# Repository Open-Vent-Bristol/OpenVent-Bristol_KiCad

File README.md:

OpenVent controller PCB, version A (KiCad) ported from version 2.7 (Altium,
incomplete), 2020-10-20, by Jeff Sutherland <jeffs@fomsystems.com>

All files for the Power Board are in the subfolder called "OV_Power". All control/main board files are in this folder level.
Electronic system diagram and overall device system diagram can be found here: https://docs.google.com/presentation/d/e/2PACX-1vRULcGT6Jc9GJDVb21LnrkGW9OiDjC7QJ2lRb0DsiA6KYFimniAMwYWqoMfq-0fJhvekxmhCl915fU4/pub?start=false&loop=true&delayms=3000&slide=id.gb10047446c_0_106
Also found by clicking "build" on https://openventbristol.co.uk/

Altium conversions aren't perfect but most everything is here.  Because the
schematic was incomplete and would not pass validation in Altium due to not
being complete a few things didn't make it across symbol-wise.  These will
have to be re-created in KiCad, but this is a trivial exercise.  Of more
import is the assigning of properties to all of the symbols in the schematics
so a sensible Bill of Materials may be generated directly from the schematic
or finished PCB layout.

All of the footprints that were currently in the Altium PCB came over and are
stored in the project footprint library.  These do not necessarily match the
schematic since the Altium PCB design reflects a former version of the
schematic as it had not been updated as yet.  So there is still much to do
before we can begin the process of creating the layout.  New mechanical
information is needed (see project documents).  The PCB layout for the former
version, stored for reference in the file "OpenVent_PCB-PcbDoc.kicad_pcb" does
not reflect the correct mechanical outline nor placement of components.  The
PCB footprints from the Altium design are missing information needed by KiCad
so if replacements are not available in the standard KiCad libraries then
these will have to be fixed.

TO DO's:
Complete schematic:
  a. Add BOM info to all symbols
  b. Complete circuit design
  c. Validate design

Process Board layout:
  a. load in missing footprints (use KiCad libraries, avoid creating
     footprints by hand if at all possible, if needed, fix existing ones.)
  b. Update PCB board outline, mech drill holes, and update placement and
     routing keepout areas
  c. Complete board placement and routing.
  d. Check association of footprints and 3D bodies; prepare STEP file of 3D
     image of board for mechanical group.

When creating symbols or updating fields in the schematic use the following
patterns for adding information to symbols in the lib or schemo:
   
   Field 0 is always 'Reference'
   Field 1 is always 'Value'
   Field 2 is always 'Footprint'
   Field 3 is always 'Datasheet'

These cannot be changed as they are required by the system.  The remaining
fields can be freely defined.  So in the case of OpenVent we need to
standardize how these are used to make sensible BOM generation possible.  For
example, something like this scheme could be used:

   Field 4 is defined as 'Val' (resistance, capacitance, inductance, etc.)
   Field 5 is defined as 'Voltage'
   Field 6 is defined as 'Tolerance'
   Field 7 is defined as 'Watt'  (usually just for resistors)
   Field 8 is defined as 'Current'  (usually for diodes and inductors)
   Field 9 is defined as 'Mfr' (manufacturer name)
   Field 10 is defined as 'Mfr_PN' (manufacturer's part number)
   Field 11 is defined as 'DistName' (this would be Farnell, DigiKey, etc.)
   Field 12 is defined as 'Dist_PN' (distributor's part number)
   Field 13 is defined as 'Detailed' (detailed description of part)

Optional fields can be added at will in the schematic to suit the needs of the
design or documentation efforts.

Notes on using KiCad:

  1. When setting up your KiCad installation you should also clone the
     repositories for the symbols, footprints and 3D models and refer to those
     in your 'manage libraries' settings rather than using the default
     libraries that came with your version of KiCad.  See github.com/kicad.

  2. Do not just add symbols to the design from the KiCad standard libraries.
     The symbols there are basically just "templates".  Copy standard symbols
     to a project library then add BOM and footprint info to the symbols if
     needed.

  3. Avoid creating your own footprints if at all possible.  Most every IC in
     common use already has a standard footprint in the KiCad libraries.

  4. All footprints should be kept in a local project library.  If
     modifications need to be made to paste or solder mask layers to deal with
     process issues copy footprints to another library and tag that library with
     the name of the PCB vendor so that managing artwork fudging among vendors can
     be easily sorted.

     After footprints are pulled into the PCB design from the standard KiCad
     libraries they may be exported to a local library to facilitate modifying any
     of their shapes to meet DFM requirements of a particular vendor.  Simply
     export the footprints to a project library from the PCB editor once the
     design has been transferred from the schematic and all the footprints
     have been accounted for.  There's no need to manually copy footprints
     from the KiCad libraries.

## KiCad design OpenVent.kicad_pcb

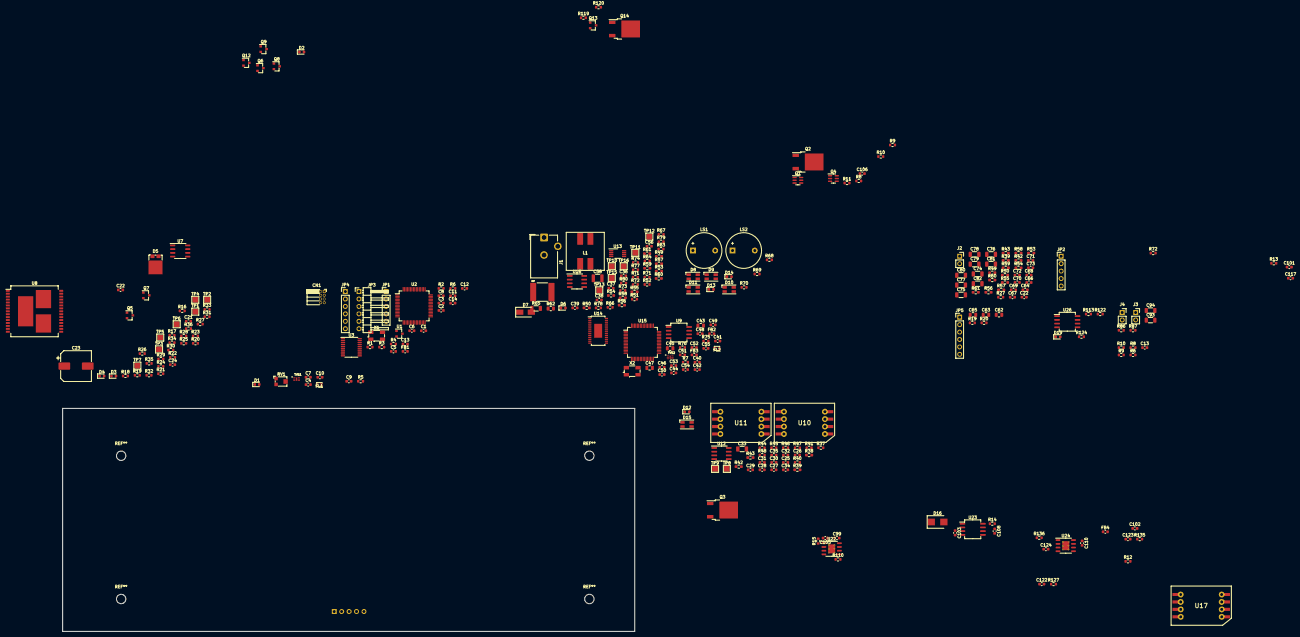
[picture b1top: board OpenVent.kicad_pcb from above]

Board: 4 copper layers, 195.5 x 76.2 mm, 290 parts (0 on the bottom side), 143 nets, no tracks yet.

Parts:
C1, C2, C3, C4, C5, C7, C8, C9, C10, C12, C14, C35, C36, C38, C40, C41, C46, C48, C49, C50, C51, C52, C53, C54, C55, C66, C122: 100nF_0603_Ceramic_Capacitor,_10%,_X7R,_25V; C_0603_1608Metric
C6, C11, C42, C44: 22pF_0603_Ceramic_Capacitor,_5%,_NP0,_50V; C_0603_1608Metric
C13, C13#2, C29, C30, C39, C68, C72, C73, C99, C103, C105, C106, C108, C110, C124: 1uF_0603_Ceramic_Capacitor,_10%,_50V,_X5R; C_0603_1608Metric
C21, C26, C28, C64, C69, C71: 470pF_0603_Ceramic_Capacitor,_5%,_100V,_C0G; C_0603_1608Metric
C22, C22#2, C24, C25, C27, C32, C37, C56, C67, C70: 10nF_0603_Ceramic_Capacitor,_10%,_50V,_X7R-; C_0603_1608Metric
C23: 1000uF_25V_Aluminium_SMD_Capacitor,_20%; CP_Elec_10x10
C31: 33nF_0603_Ceramic_Capacitor,_10%,_50V; C_0603_1608Metric
C33: 22uF_1206_Ceramic_Capacitor,_10%,_10V,_X7R; C_1206_3216Metric
C34: 033uF_0603_Ceramic_Capacitor,_10%,_16V; C_0603_1608Metric
C43, C45, C47, C62, C63, C65: 10uF_0805_Ceramic_Capacitor_10%_X7R_10V; C_0805_2012Metric
C57: 2.2uF_2824_film_capacitor_10%_40V; CAPPC7360X380N
C58: C_1210_10uF_25V_10%_X7R; C_1210_3225Metric
C74, C75, C76, C77, C78, C79, C80, C81, C82: C_1206_47nF_16V_2%_PPS_film; C_1206_3216Metric
C93, C94: 22uF_1206_Ceramic_Capacitor,_10%,_10V,_X7R; R_1206_3216Metric
C101, C102, C117, C123: 2.2uF_0603_Ceramic_Capacitor,_10%,_50V,_X5R; C_0603_1608Metric
CN1: 2x5_Way_1.27mm_Pitch_Header_MCU; PinSocket_2x04_P1.27mm_Horizontal
D1, D2, D3, D6, D12, D14, D19: LED_GREEN_0603_SMD; LED_0603_1608Metric
D4, D13: LED_Red_0603_SMD; LED_0603_1608Metric
D5: FSV20100V; TO-277A
D7: DIODE_GEN_PURP_1KV_1A_SMA; D_SMA
D8, D9, D10, D11, D15: BB-HRGB32M-TRB; LED_RGB_BL-RRGB32M_TRB_PLCC4_3.2x2.8mm
D16: MBRS260T3G; D_SMB
FB1, FB2, FB3: Chip_Ferrite,_600R,_0603,_750mA; L_0603_1608Metric
FB4: BLM18AG601SN1D Chip_Ferrite,_600R,_0603,_750mA; C_0603_1608Metric
FL1, FL2: DLP11SA900HL2L; Murata_DLP11S
J1: OpenVent_Barrel_Connector; BarrelJack_CUI_PJ-102AH_Horizontal
J2, J3, J4: Conn_01x02; PinSocket_1x02_P2.54mm_Vertical
JP1, JP2, JP2#2: Pin_Header,_1x5-Way,_2.54mm_Pitch; PinHeader_1x05_P2.54mm_Vertical
JP3: Pin_Header,_1x6-Way,_2.54mm_Pitch, Mpn 640456-6; PinHeader_1x06_P2.54mm_Horizontal
JP4, JP5: Pin_Header,_1x6-Way,_2.54mm_Pitch; PinHeader_1x06_P2.54mm_Vertical
L1: MSD1260-333; MSD1260
LS1, LS2: AUDIO_MAGNETIC_INDICATOR; Buzzer_12x9.5RM7.6
Q1, Q4: DMMT5401-7-F; SC-74-6_1.5x2.9mm_P0.95mm
Q2, Q3, Q14: AOD4185; TO-252-2
Q5, Q6, Q7, Q9, Q12, Q13: 2N7002BK; SOT-23
Q8: SSM3K341R; SOT-23
R1, R2, R3: R_0603_2k74_0.1W_0.1%; R_0603_1608Metric
R4, R9, R9#2, R11, R12, R21, R22, R26, R28, R31, R71, R73, R74, R75, R76: 1K_0603_Chip_Resistor,_1%,_0.1W; R_0603_1608Metric
R5, R6, R6#2, R16, R18, R52, R119, R120, R124: 10k_0603_Chip_Resistor,_1%,_0.1W; R_0603_1608Metric
R7, R72, R72#2, R86, R87: 12k_0603_Chip_Resistor,_1%,_0.1W; R_0603_1608Metric
R8, R8#2, R10, R10#2, R29, R68, R69, R110, R127: 100K_0603_Chip_Resistor,_1%,_0.1W; R_0603_1608Metric
R13, R14, R15, R36, R113, R122, R135, R136: 0R1_0603_Chip_Resistor,_1%,_0.1W; R_0603_1608Metric
R17, R23, R37, R41, R67: 215k_0603_Chip_Resistor,_1%,_0.1W; R_0603_1608Metric
R19, R19#2, R20, R20#2: 2k4_0603_Chip_Resistor,_1%,_0.1W; R_0603_1608Metric
R24, R25: 4k7_0603_Chip_Resistor,_1%,_0.1W; R_0603_1608Metric
R27, R27#2: 18k_0603_Chip_Resistor,_1%,_0.1W; R_0603_1608Metric
R30, R32, R35: 30k_0603_Chip_Resistor,_1%,_0.1W; R_0603_1608Metric
R33, R34: 20k_0603_Chip_Resistor,_1%,_0.1W; R_0603_1608Metric
R38, R39, R39#2, R42, R42#2, R43, R43#2, R49, R49#2, R50, R50#2, R53, R53#2, R54, R54#2, R55, R55#2, R56, R56#2, R57, R57#2, R58, R58#2, R59, R59#2, R60, R60#2, R61, R61#2: R_0603_47K_0.1%_0.1W_Film; R_0603_1608Metric_Pad0.98x0.95mm_HandSolder
R40, R44, R66: 1M_0603_Chip_Resistor,_1%,_0.1W; R_0603_1608Metric
R45, R46: 3k6_0603_Chip_Resistor,_1%,_0.1W; R_0603_1608Metric
R47, R48: 180k_0603_Chip_Resistor,_1%,_0.1W; R_0603_1608Metric
R51: 634R_0603_Chip_Resistor,_1%,_0.1W; R_0603_1608Metric
R62: R_0805_050m_cursense; R_0805_2012Metric
R63: R_0603_015m_cursense; R_0603_1608Metric
R64: R_0603_49k9_0.1W_1%; R_0603_1608Metric
R65: R_1206_250m_cursense; R_1206_3216Metric
R70: 10R_0603_Chip_Resistor,_1%,_0.1W; R_0603_1608Metric
R77: R_0603_113k_0.1W_1%; R_0603_1608Metric
R78: R_0603_30k1_0.1W_1%; R_0603_1608Metric
R79: R_0603_95k3_0.1W_1%; R_0603_1608Metric
R80: R_0603_10k2_0.1W_1%; R_0603_1608Metric
RT1: R_Thermistor_0603_10K_NTC; R_0603_1608Metric
RV1: RES_trimpot_10K_SMD; Potentiometer_Bourns_TC33X_Vertical
TP1, TP2, TP3, TP4, TP5, TP6, TP7, TP8, TP9, TP10, TP11, TP12, TP13, TP15, TP16: Test_Point_PTH; TestPoint_Pad_2.0x2.0mm
TVS1, TVS2: RClamp3654P.TCT; SON50P160X160X65-7N
U1: TMP236A4DBZT; SOT-23
U2: STM32L476RGLQFP64; LQFP-64_10x10mm_P0.5mm
U3: TI_TXB0108PWR; TSSOP-20_4.4x6.5mm_P0.65mm
U7: LMC6772AIMX; SO-8_3.9x4.9mm_P1.27mm
U8: VNH5019ATR-E; ST_MultiPowerSO-30
U9, U23, U26: LDL212D33R; SO-8_5.3x6.2mm_P1.27mm
U10, U17: MPXV4006GP; NXP-CASE-1369_482C
U11: MPXV4006DP; NXP-CASE-1351-482C
U12, U16: TLV2333IDR; SOIC-8_3.9x4.9mm_P1.27mm
U13: TLV7042DGKR; VSSOP-8_3.0x3.0mm_P0.65mm
U14: LT3796; TSSOP-28-LTvar_EB_4.4x9.7mm_P0.65mm
U15: FT2232HL-REEL; LQFP-64_10x10mm_P0.5mm
U22, U24: BD50FC0WEFJ-E2; HSOP-8-1EP_3.9x4.9mm_P1.27mm_EP2.41x3.1mm_ThermalVias
X1: ABM3B-16.000MHZ; Crystal_SMD_Abracon_ABM3B-4Pin_5.0x3.2mm
X2: ABM3B-12.000MHZ; Crystal_SMD_Abracon_ABM3B-4Pin_5.0x3.2mm

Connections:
+3.3V: C65.1, C123.1, R122.2, R135.2
+3V3: C2.2, C41.1, C106.2, C117.1, C122.2, CN1.1, FB2.1, FB3.1, JP1.2, JP3.6, R13.2, R19.2, R19#2.2, R20.2, R20#2.2, R24.2, R25.2, R52.1, R71.1, R73.1, R76.1, R86.1, R87.1, R119.2, TP10.1, U1.1, U3.2, U3.10, U7.6, U13.8, U15.20, U15.31, U15.42, U15.50, U15.56
+5V: C12.2, C14.2, C22.2, C22#2.2, C25.2, C27.2, C29.2, C30.2, C35.2, C62.1, C63.1, C67.2, C68.2, C70.2, C72.2, C73.2, C99.2, C101.1, C102.1, C105.2, C110.2, C124.2, D8.1, D9.1, D10.1, D11.1, D15.1, FB4.1, JP1.1, LS1.1, LS2.1, R1.1, R3.1, R15.2, R29.2, R69.2, R113.2, R120.2, R136.2, RV1.1, TP11.1, U3.19, U7.8, U10.2, U12.8, U17.2, U22.8, U24.8, U26.4
/JTAG/J_3V3: C52.1, C53.1, C54.1, C55.1, U9.1, U9.8
/Microcontroller/ANALOG-SPARE: JP1.3, U2.17
/Microcontroller/BUZZER_PWM: R8.1, R8#2.1, U2.16
/Microcontroller/USB-DM: FL1.2, TVS1.1, U2.44
/Microcontroller/USB-DP: FL1.3, TVS1.2, U2.45
/Microcontroller/XTAL-1: C6.2, U2.5, X1.1
/Microcontroller/XTAL-2: C11.2, U2.6, X1.3
/Power_Supplies/3v3_S: R122.1, U26.1, U26.8
AD_VREF: C75.1, R38.2
FLOW_SENS_DRCT: C69.2, R37.1, R57.1, R57#2.1
FLOW_SENS_GAIN: C32.1, R44.2, R58.1, R58#2.1, U12.7
GND: C1.1, C2.1, C3.1, C4.1, C5.1, C6.1, C7.1, C8.1, C9.1, C10.1, C11.1, C12.1, C13.1, C13#2.1, C14.1, C22.1, C22#2.1, C25.1, C26.1, C27.1, C28.1, C29.1, C30.1, C31.2, C33.2, C35.1, C36.2, C37.2, C38.2, C39.2, C40.2, C41.2, C42.2, C43.2, C44.2, C45.2, C46.2, C47.2, C48.2, C49.2, C50.2, C51.2, C52.2, C53.2, C54.2, C55.2, C56.2, C58.2, C62.2, C63.2, C64.1, C65.2, C66.1, C67.1, C68.1, C69.1, C70.1, C71.1, C72.1, C73.1, C74.2, C75.2, C76.2, C77.2, C78.2, C79.2, C80.2, C81.2, C82.2, C93.2, C94.2, C99.1, C101.2, C102.2, C103.1, C105.1, C106.1, C108.2, C110.1, C117.2, C122.1, C123.2, C124.1, CN1.3, CN1.5, D1.2, D5.1, D5.2, D8.3, D9.3, D10.3, D11.3, D12.2, D14.2, D15.3, J1.2, J2.2, JP1.4, JP1.5, JP2.1, JP2#2.1, JP3.5, JP4.1, JP5.1, L1.4, Q5.2, Q9.2, Q12.2, R2.2, R7.1, R8.2, R8#2.2, R10.2, R10#2.2, R11.1, R12.1, R18.2, R27.1, R27#2.1, R33.2, R34.2, R40.1, R41.1, R46.1, R47.2, R63.1, R67.2, R68.2, R70.2, R72.1, R72#2.1, R74.1, R75.1, R80.2, R110.1, RV1.3, TP2.1, TP9.1, TP13.1, TP16.1, TVS1.7, TVS2.7, U1.3, U2.12, U2.18, U2.31, U2.47, U2.63, U3.11, U7.4, U7.5, U9.2, U9.3, U9.6, U9.7, U10.3, U11.3, U12.4, U13.4, U14.4, U14.13, U14.17, U14.21, U14.22, U14.29, U15.1, U15.5, U15.10, U15.11, U15.13, U15.15, U15.25, U15.35, U15.47, U15.51, U16.4, U17.3, U22.3, U22.9, U23.2, U23.3, U23.6, U23.7, U24.3, U24.9, U26.2, U26.3, U26.6, U26.7
I2C_SCL: R20.1, R20#2.1
I2C_SDA: R19.1, R19#2.1
LDO-EN: R110.2, U22.5, U24.5
MOTOR-CURRENT: C21.2, R23.1, TP3.1, U2.9, U7.1
MOTOR-IN-B: R21.1, U2.34
NRST_M: R6.1, R6#2.1, U2.7
unnamed: C3.2, FB1.2, U2.13
unnamed: C13.2, C13#2.2, R9.1, R9#2.1
unnamed: C21.1, R18.1, R23.2, U7.2
unnamed: C24.1, Q7.1, R34.1, R35.1, TP7.1
unnamed: C31.1, R37.2, R40.2, U12.5
unnamed: C32.2, R41.2, R44.1, U12.6
unnamed: C33.1, R45.2, R47.1, U12.3
unnamed: C34.1, R46.2, R48.1, U12.2
unnamed: C36.1, R52.2, U13.3
unnamed: C37.1, U14.28
unnamed: C38.1, U14.11
unnamed: C40.1, U9.4, U9.5
unnamed: C42.1, U15.2, X2.1
unnamed: C43.1, C46.1, FB3.2, U15.4
unnamed: C44.1, U15.3, X2.3
unnamed: C47.1, C48.1, FB2.2, U15.9
unnamed: C57.1, L1.1, Q8.3
unnamed: C57.2, D16.2, L1.2
unnamed: C58.1, D16.1, R65.1, U14.1
unnamed: C74.1, FB4.2
unnamed: C103.2, U23.4, U23.5
unnamed: U8.15, U8.16, U8.21
unnamed: U8.1, U8.25, U8.30
unnamed: D1.1, R4.1
unnamed: Q1.5, Q2.3, Q3.3, Q4.5
unnamed: D5.3, R36.1
unnamed: D7.1, R65.2, R78.1, RT1.1, U14.2
unnamed: D10.2, D11.4
unnamed: D9.2, D10.4
unnamed: D11.2, U15.60
unnamed: FL2.2, TVS2.1, U15.7
unnamed: FL2.3, TVS2.2, U15.8
unnamed: J2.1, R45.1, TP8.1
unnamed: JP2.2, JP2#2.2
unnamed: JP2.3, JP2#2.3
unnamed: JP2.4, JP2#2.4
unnamed: JP2.5, JP2#2.5
unnamed: L1.3, R62.2, U14.26
unnamed: LS1.2, LS2.2, Q13.3
unnamed: Q1.1, Q1.2, Q1.3
unnamed: Q1.4, Q3.1
unnamed: Q2.1, Q4.4
unnamed: Q4.1, Q4.2, Q4.3
unnamed: Q5.3, Q6.1, R29.1
unnamed: Q6.2, Q7.2, R33.1, TP6.1
unnamed: Q7.3, R32.1, TP5.1
unnamed: Q8.1, U14.19
unnamed: Q8.2, R63.2, U14.18
unnamed: Q9.1, R68.1
unnamed: Q12.1, R64.2, U14.16
unnamed: Q12.3, R77.2
unnamed: Q9.3, Q13.1, R69.1
unnamed: Q6.3, Q14.1, R30.1, TP4.1
unnamed: R1.2, R2.1, R3.2
unnamed: R4.2, U2.4
unnamed: R5.1, U2.60
unnamed: R7.2, U15.6
unnamed: R9.2, R9#2.2, R10.1, R10#2.1
unnamed: R14.1, U23.1, U23.8
unnamed: R15.1, U22.1
unnamed: R16.1, R17.1, U7.3
unnamed: R16.2, TP1.1, U8.18, U8.19, U8.20, U8.26, U8.27, U8.28
unnamed: R21.2, U8.10
unnamed: R22.2, U8.7
unnamed: R27.2, R27#2.2
unnamed: R39.2, R39#2.2
unnamed: R42.2, R42#2.2
unnamed: R43.2, R43#2.2
unnamed: R49.2, R49#2.2, U13.2
unnamed: R50.2, R50#2.2
unnamed: R53.2, R53#2.2, U14.6
unnamed: R54.2, R54#2.2
unnamed: R64.1, U14.20
unnamed: R66.2, R67.1, U16.3
unnamed: R71.2, U13.6
unnamed: R72.2, R72#2.2, U13.5
unnamed: R73.2, U16.6
unnamed: R74.2, U16.5
unnamed: R75.2, U15.61
unnamed: R76.2, U15.14
unnamed: R77.1, R79.2, R80.1, U14.7
unnamed: R78.2, R79.1, RT1.2
unnamed: R136.1, U24.1
unnamed: U2.28, U3.4
unnamed: U2.56, U3.6
unnamed: U2.57, U3.7
unnamed: U2.58, U3.8
unnamed: U2.59, U3.9
unnamed: U14.9, U14.10, U14.14
O2_SENS: C34.2, R48.2, R59.1, R59#2.1, U12.1
PB_SEL_MCU: R28.2, U2.14
PRES_SENS_PAT: C71.2, R56.1, R56#2.1, U10.4
PRES_SENS_VENT: C64.2, R55.1, R55#2.1, U17.4
PWM: R22.1, U2.15
SOUNDER-CURRENT: Q13.2, R70.1
SPI1_FPGA_CS: JP3.4, U2.20
SPI1_MISO: JP3.3, U2.22
SPI1_MOSI: JP3.2, U2.23
SPI1_SCLK: JP3.1, U2.21
SensorOut_F: R60.1, R60#2.1
SensorOut_G: R61.1, R61#2.1
TCK_M: CN1.4, U2.49
TDI_M: CN1.8, U2.50
TDO_M: CN1.6, U2.55
TMS_M: CN1.2, U2.46
V1V8: C45.1, C49.1, C50.1, C51.1, U15.12, U15.37, U15.49, U15.64
VBATT-SCALED: U2.10, U16.1, U16.2
VBUS: C39.1, D7.2, Q4.6, R66.1, TP12.1, TP15.1
VDC: C4.2, C5.2, C7.2, C8.2, C9.2, C10.2, C108.1, D2.1, D19.1, R5.2, R6.2, R6#2.2, R14.2, R124.2, U2.1, U2.19, U2.32, U2.48, U2.64, U16.8
VIN: J1.1, R51.1, R62.1, U14.23, U14.25
VIN_FAIL_M: R124.1, U2.61
VMEM: C1.2, Q1.6, TVS1.6
VMOTOR: C24.2, R35.2, R36.2, U8.3, U8.12, U8.13, U8.23
Vcap_F: C81.1, R53.1, R53#2.1, R60.2, R60#2.2
Vcap_FLOW_SENS_DRCT: C78.1, R43.1, R43#2.1, R57.2, R57#2.2
Vcap_FLOW_SENS_GAIN: C79.1, R49.1, R49#2.1, R58.2, R58#2.2
Vcap_G: C82.1, R54.1, R54#2.1, R61.2, R61#2.2
Vcap_O2_SENS: C80.1, R50.1, R50#2.1, R59.2, R59#2.2
Vcap_PRES_SENS_PAT: C77.1, R42.1, R42#2.1, R56.2, R56#2.2
Vcap_PRES_SENS_VENT: C76.1, R39.1, R39#2.1, R55.2, R55#2.2
nMOTOR-FAULT-A: R25.1, U2.37, U8.5
nMOTOR-FAULT-B: R24.1, U2.25, U8.9

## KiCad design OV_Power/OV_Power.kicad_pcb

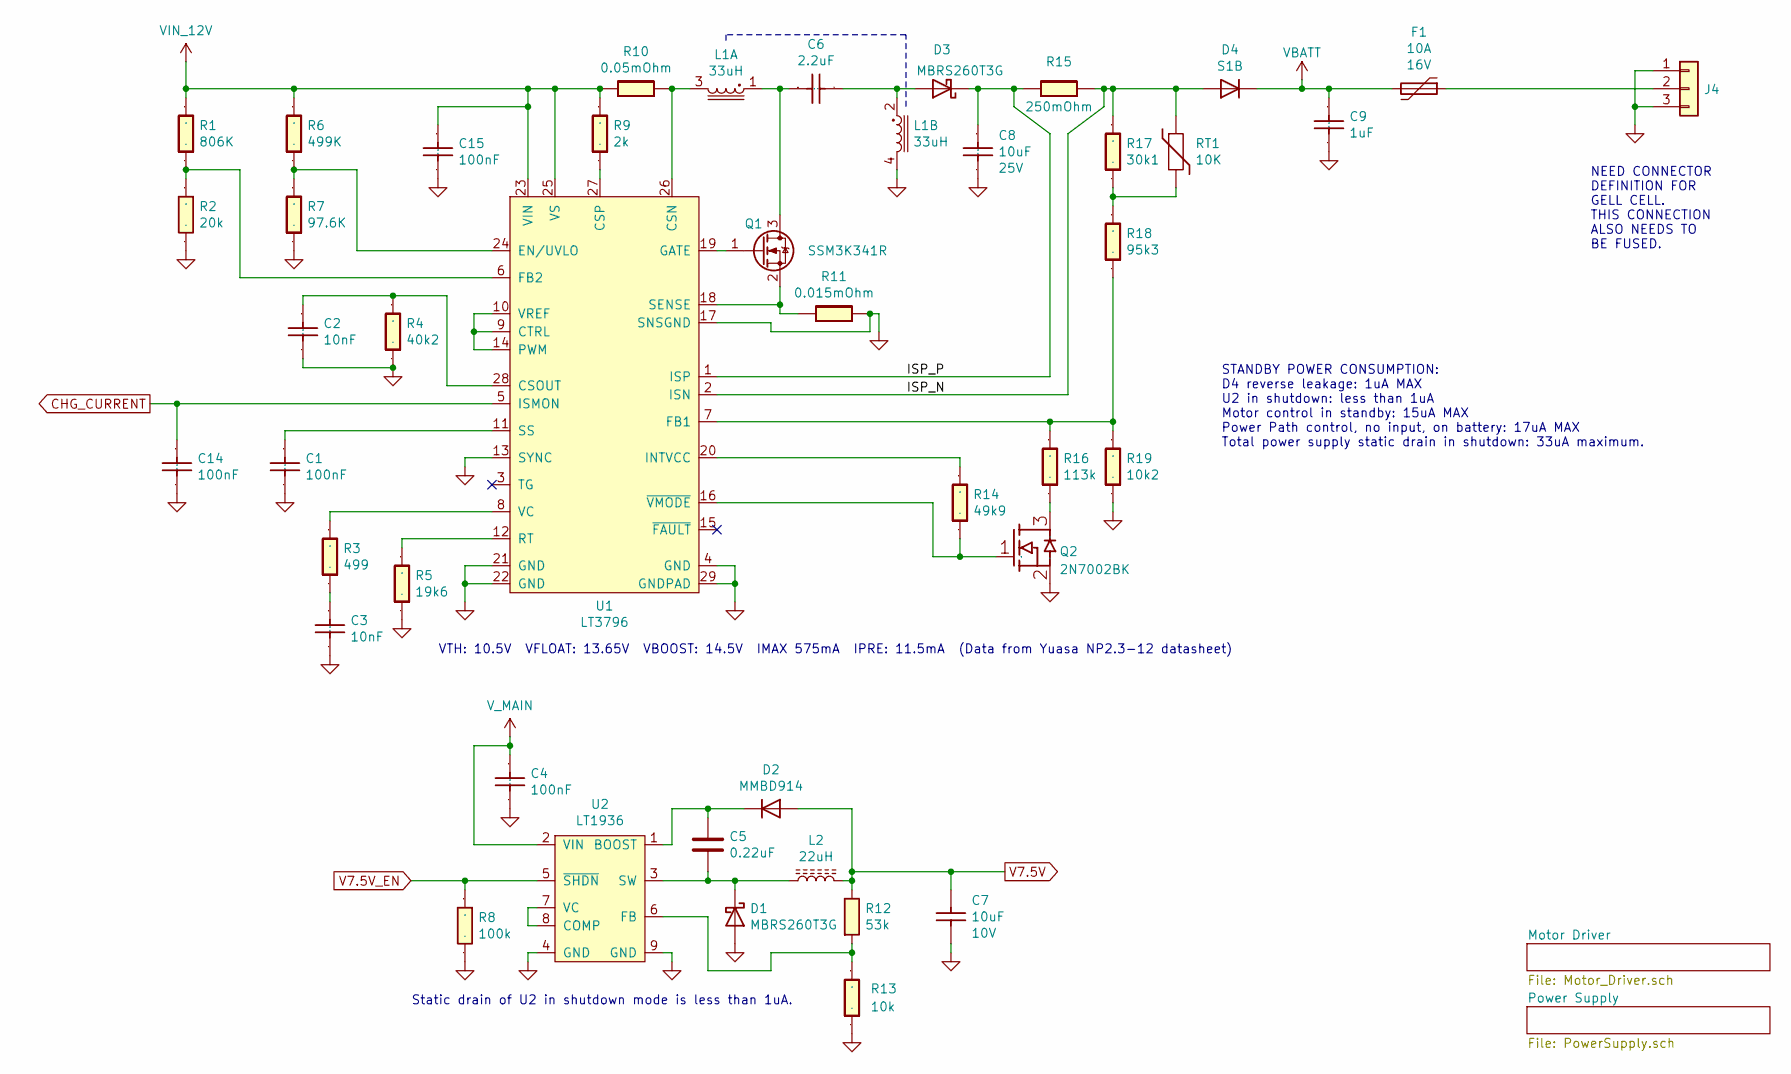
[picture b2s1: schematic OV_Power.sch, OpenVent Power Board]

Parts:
C1, C4, C14, C15: 100nF_0603_Ceramic_Capacitor,_10%,_X7R,_25V; C_0603_1608Metric; Voltage 25V; Tolerance 10%
C2, C3: 10nF_0603_Ceramic_Capacitor,_10%,_50V,_X7R-; C_0603_1608Metric; Voltage 50V; Tolerance 10%
C5: C_0603_0.22uf_25V_10%; C_0603_1608Metric; Tolerance 10%; Voltage 25V; Mfr_PN GCM188R71E224KA55J
C6: 2.2uF_2824_film_capacitor_10%_40V; CAPPC7360X380N; Voltage 63V; Tolerance 10%; Mfr_PN SMDTC04220TB00KQ00
C7: 10uF_0805_Ceramic_Capacitor_10%_X7R_10V; C_0805_2012Metric; Voltage 10V; Tolerance 10%; Mfr_PN GCM21BR71A106KE22L
C8: C_1210_10uF_25V_10%_X7R; C_1210_3225Metric; Voltage 25V; Tolerance 10%; Mfr_PN CL32A106KAULNNE
C9: 1uF_0603_Ceramic_Capacitor,_10%,_50V,_X5R; C_0603_1608Metric; Voltage 50V; Tolerance 10%
D1, D3: MBRS260T3G; D_SMB; Voltage 60V; Mfr_PN MBRS260T3G
D2: MMBD914; SOT-23; Voltage 100V; Mfr_PN MMBD914-E3-08
D4: S1B; D_SMA; Voltage 100V; Mfr_PN S1B
F1: Polyfuse_10A; LF_16R1000G; Voltage 16V; Mfr_PN 16R1000GMR
J4: Conn_01x03_JST_B3P_Vert; JST_B3P-VH(LF)(SN); Mfr_PN B3P-VH(LF)(SN)
L1: MSD1260-333; MSD1260; Mfr_PN MSD1260-333MLB
L2: L_22uH_2.6A_42mOhm_SMT; L-Bourns-SRU1048-series; Mfr_PN SRU1048-220Y
Q1: SSM3K341R; SOT-23; Mfr_PN SSM3K341R,LF
Q2: 2N7002BK; SOT-23; Voltage 60V; Mfr_PN 2N7002BK,215
R1: R_0603_806K_0.1W_1%; R_0603_1608Metric; Tolerance 1%
R2: 20k_0603_Chip_Resistor,_1%,_0.1W; R_0603_1608Metric; Tolerance 1%
R3: R_0603_499R_0.1W_1%; R_0603_1608Metric; Tolerance 1%
R4: R_0603_40k2K_0.1W_1%; R_0603_1608Metric; Tolerance 1%
R5: R_0603_19k6_0.1W_1%; R_0603_1608Metric; Tolerance 1%
R6: R_0603_499K_0.1W_1%; R_0603_1608Metric; Tolerance 1%
R7: R_0603_97.6K_0.1W_1%; R_0603_1608Metric; Tolerance 1%
R8: 100K_0603_Chip_Resistor,_1%,_0.1W; R_0603_1608Metric; Tolerance 1%
R9: R_0603_2k_0.1W_1%; R_0603_1608Metric; Tolerance 1%
R10: R_0805_050m_cursense; R_0805_2012Metric; Tolerance 1%; Mfr_PN KDV08FR050ET
R11: R_0603_015m_cursense; R_0603_1608Metric; Tolerance 1%; Mfr_PN LVT06R0150FER
R12: R_0603_53K_0.1W_1%; R_0603_1608Metric; Tolerance 1%; Mfr_PN RN73H1JTTD5302F25
R13: 10k_0603_Chip_Resistor,_1%,_0.1W; C_0603_1608Metric; Tolerance 1%
R14: R_0603_49k9_0.1W_1%; R_0603_1608Metric; Tolerance 1%
R15: R_1206_250m_cursense; R_1206_3216Metric; Tolerance 1%; Mfr_PN PT1206FR-7W0R25L
R16: R_0603_113k_0.1W_1%; R_0603_1608Metric; Tolerance 1%
R17: R_0603_30k1_0.1W_1%; R_0603_1608Metric; Tolerance 1%
R18: R_0603_95k3_0.1W_1%; R_0603_1608Metric; Tolerance 1%
R19: R_0603_10k2_0.1W_1%; R_0603_1608Metric; Tolerance 1%
RT1: R_Thermistor_0603_10K_NTC; R_0603_1608Metric; Tolerance 5%; Mfr_PN NTHS0603N02N1002JE
U1: LT3796; TSSOP-28-LTvar_EB_4.4x9.7mm_P0.65mm; Mfr_PN LT3796IFE-1#TRPBF
U2: LT1936; LT_MS8E; Mfr_PN LT1936EMS8E#PBF

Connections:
/ISP_N: D4.2 (A), R15.2, R17.1, RT1.1, U1.2 (ISN)
/ISP_P: C8.1, D3.1 (K), R15.1, U1.1 (ISP)
CHG_CURRENT: C14.1, U1.5 (ISMON); also elsewhere on the board
GND: C1.2, C2.2, C3.2, C4.2, C7.2, C8.2, C9.2, C14.2, C15.2, D1.2 (A), J4.1, J4.3, L1.4, Q2.2 (S), R2.2, R4.2, R5.2, R7.2, R8.2, R11.1, R13.2, R19.2, U1.4 (GND), U1.13 (SYNC), U1.17 (SNSGND), U1.21 (GND), U1.22 (GND), U1.29 (GNDPAD), U2.4 (GND), U2.9 (GND); also elsewhere on the board
unnamed: C1.1, U1.11 (SS)
unnamed: C2.1, R4.1, U1.28 (CSOUT)
unnamed: C3.1, R3.2
unnamed: C5.1, D2.3 (K), U2.1 (BOOST)
unnamed: C5.2, D1.1 (K), L2.1, U2.3 (SW)
unnamed: C6.1, L1.1 (2), Q1.3 (D)
unnamed: C6.2, D3.2 (A), L1.2
unnamed: F1.1, J4.2
unnamed: L1.3 (4), R10.2, U1.26 (CSN)
unnamed: Q1.1 (G), U1.19 (GATE)
unnamed: Q1.2 (S), R11.2, U1.18 (SENSE)
unnamed: Q2.1 (G1), R14.2, U1.16 (~VMODE~)
unnamed: Q2.3 (D), R16.2
unnamed: R1.2, R2.1, U1.6 (FB2)
unnamed: R3.1, U1.8 (VC)
unnamed: R5.1, U1.12 (RT)
unnamed: R6.2, R7.1, U1.24 (EN/UVLO)
unnamed: R9.2, U1.27 (CSP)
unnamed: R12.2, R13.1, U2.6 (FB)
unnamed: R14.1, U1.20 (INTVCC)
unnamed: R16.1, R18.2, R19.1, U1.7 (FB1)
unnamed: R17.2, R18.1, RT1.2
unnamed: U1.9 (CTRL), U1.10 (VREF), U1.14 (PWM)
unnamed: U2.7 (VC), U2.8 (COMP)
V7.5V: C7.1, D2.1 (A), L2.2, R12.1; also elsewhere on the board
V7.5V_EN: R8.1, U2.5 (~SHDN~); also elsewhere on the board
VBATT: C9.1, D4.1 (K), F1.2; also elsewhere on the board
VIN_12V: C15.1, R1.1, R6.1, R9.1, R10.1, U1.23 (VIN), U1.25 (VS); also elsewhere on the board
V_MAIN: C4.1, U2.2 (VIN); also elsewhere on the board

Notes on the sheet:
VTH: 10.5V VFLOAT: 13.65V VBOOST: 14.5V IMAX 575mA IPRE: 11.5mA (Data from Yuasa NP2.3-12 datasheet)
NEED CONNECTOR DEFINITION FOR GELL CELL. THIS CONNECTION ALSO NEEDS TO BE FUSED.
Static drain of U2 in shutdown mode is less than 1uA.
STANDBY POWER CONSUMPTION: D4 reverse leakage: 1uA MAX U2 in shutdown: less than 1uA Motor control in standby: 15uA MAX Power Path control, no input, on battery: 17uA MAX Total power supply static drain in shutdown: 33uA maximum.

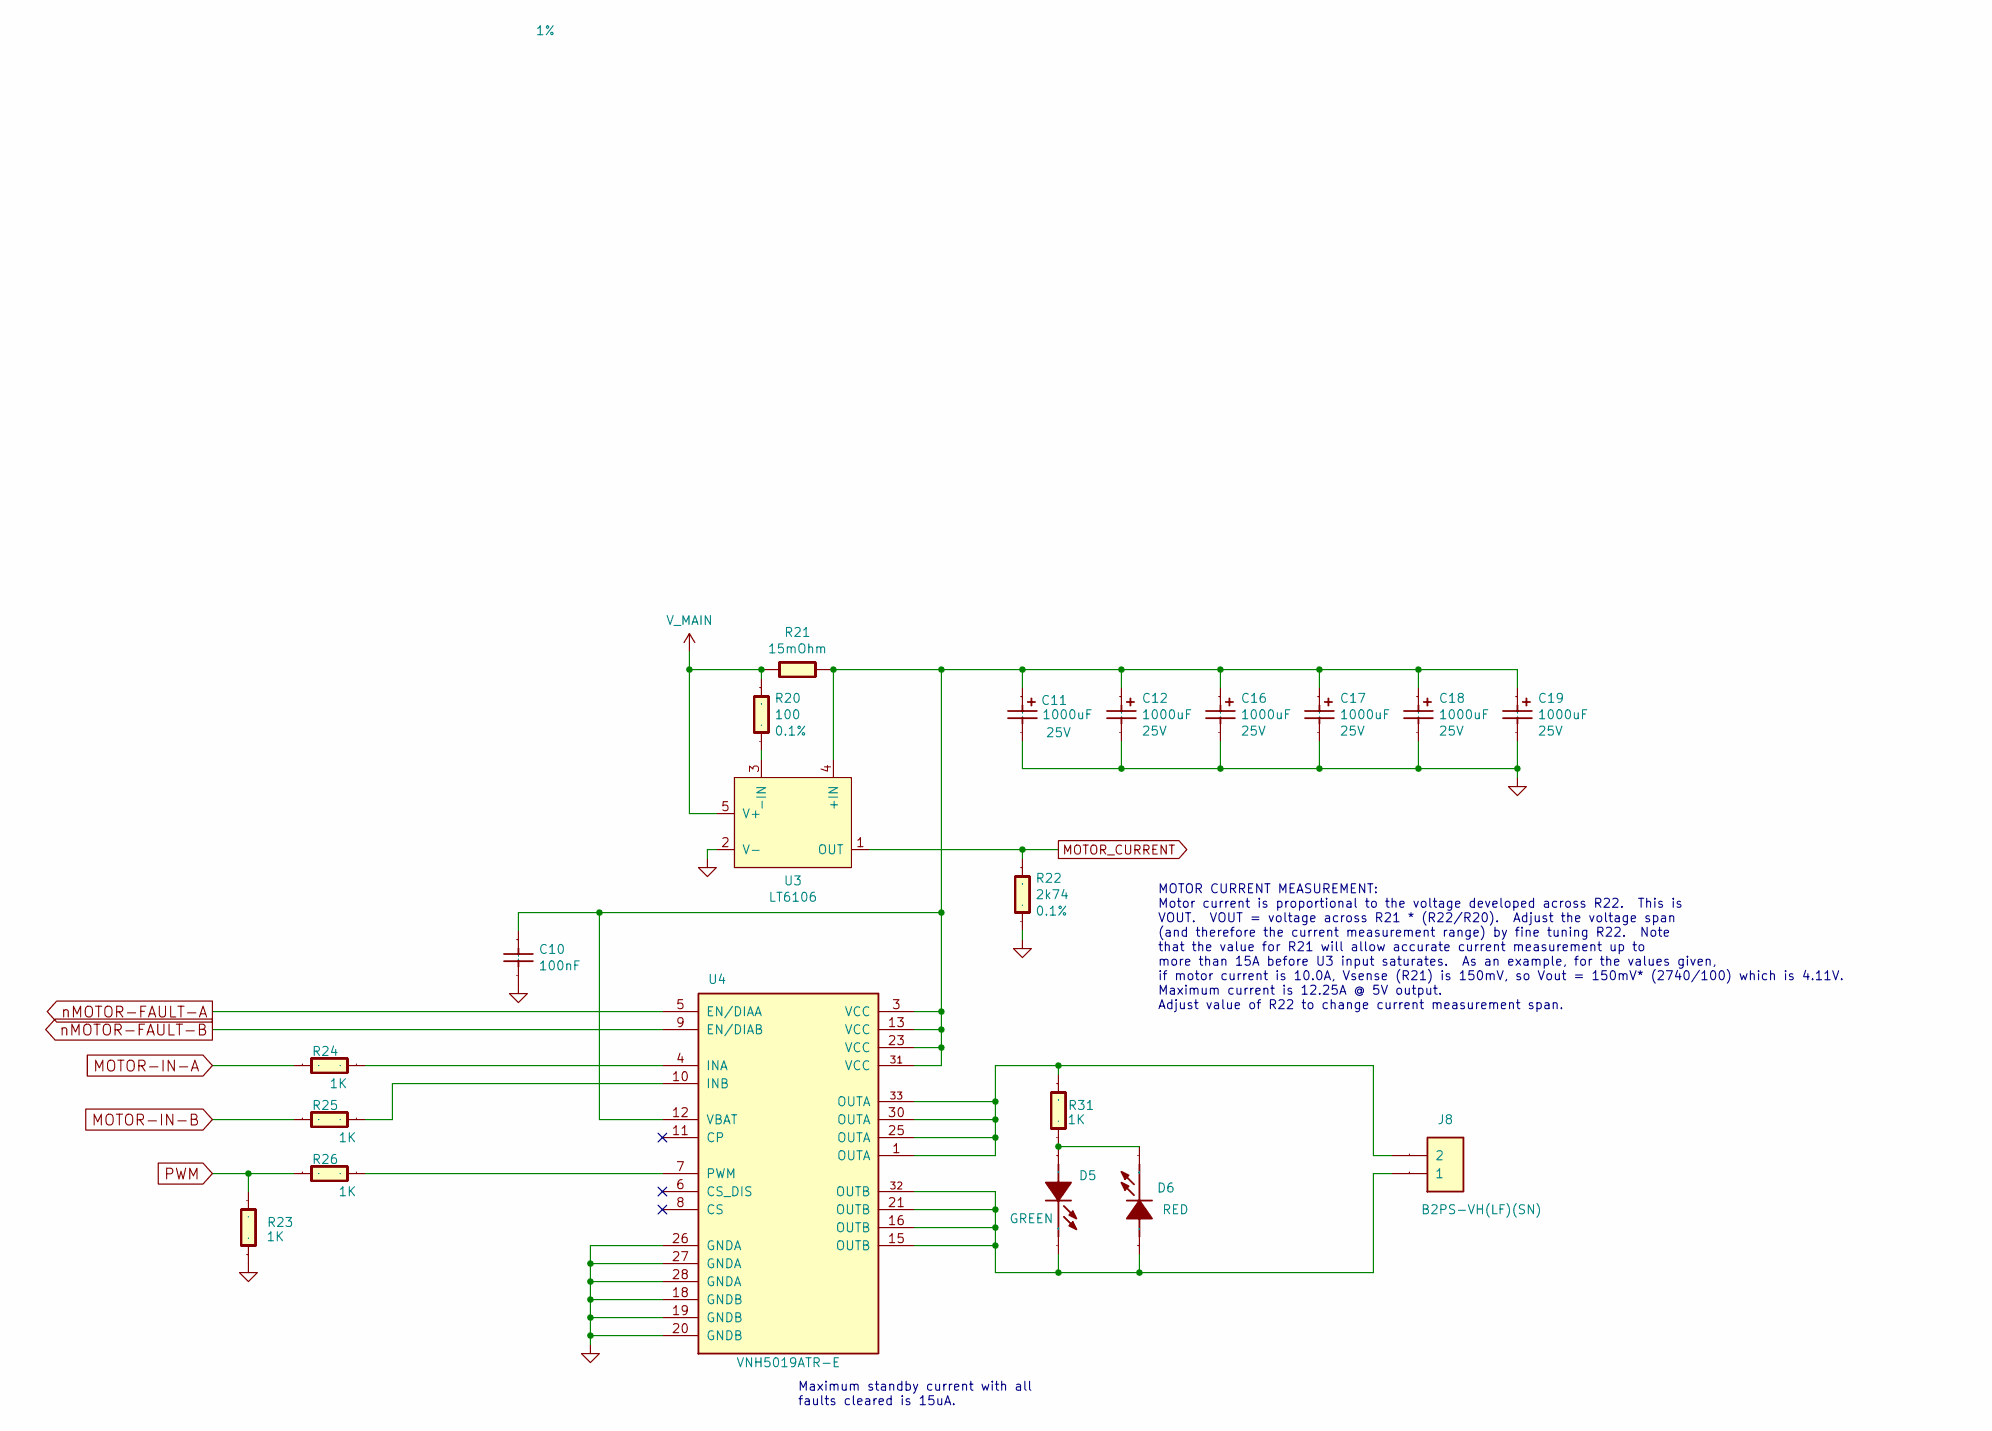
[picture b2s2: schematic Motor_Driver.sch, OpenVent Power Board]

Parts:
C10: 100nF_0603_Ceramic_Capacitor,_10%,_X7R,_25V; C_0603_1608Metric; Voltage 25V; Tolerance 10%
C11, C12, C16, C17, C18, C19: 1000uF_25V_Aluminium_SMD_Capacitor,_20%; CP_Elec_10x10; Voltage 25V; Tolerance 20%; Mfr_PN EMZS250ARA102MJA0G
D5: LED_GREEN_0603_SMD; LED_0603_1608Metric; Mfr_PN SML-D12M8WT86C
D6: LED_Red_0603_SMD; LED_0603_1608Metric; Mfr_PN LTST-C193KRKT-5A
J8: CONN_HEADER_R_A_2POS_JST_10A; JST_B2PS-VHLSN; Mfr_PN B2PS-VH(LF)(SN)
R20: R_0603_100_0.1W_0.1%; R_0603_1608Metric; Tolerance 0.1%; Mfr_PN RT0603BRD07100RL
R21: R_2512_15m_cursense; R_2512_6332Metric; Tolerance 1%; Mfr_Pn CSR2512A0R015F
R22: R_0603_2k74_0.1W_0.1%; R_0603_1608Metric; Tolerance 0.1%; Mfr_PN RT0603BRE072K74L
R23, R24, R25, R26, R31: 1K_0603_Chip_Resistor,_1%,_0.1W; R_0603_1608Metric; Tolerance 1%
U3: LT6106; TSOT-23-5; Mfr_PN LT6106IS5#TRPBF
U4: VNH5019ATR-E; ST_MultiPowerSO-30; Mfr_PN VNH5019ATR-E

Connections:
GND: C10.2, C11.2 (-), C12.2 (-), C16.2 (-), C17.2 (-), C18.2 (-), C19.2 (-), R22.2, R23.1, U3.2 (V-), U4.18 (GNDB), U4.19 (GNDB), U4.20 (GNDB), U4.26 (GNDA), U4.27 (GNDA), U4.28 (GNDA); also elsewhere on the board
MOTOR-IN-A: R24.1; also elsewhere on the board
MOTOR-IN-B: R25.1; also elsewhere on the board
MOTOR_CURRENT: R22.1, U3.1 (OUT); also elsewhere on the board
unnamed: C10.1, C11.1 (+), C12.1 (+), C16.1 (+), C17.1 (+), C18.1 (+), C19.1 (+), R21.2, U3.4 (+IN), U4.3 (VCC), U4.12 (VBAT), U4.13 (VCC), U4.23 (VCC), U4.31 (VCC)
unnamed: D5.1 (ANODE), D6.2 (CATHODE), R31.2
unnamed: D5.2 (CATHODE), D6.1 (ANODE), J8.1, U4.15 (OUTB), U4.16 (OUTB), U4.21 (OUTB), U4.32 (OUTB)
unnamed: J8.2, R31.1, U4.1 (OUTA), U4.25 (OUTA), U4.30 (OUTA), U4.33 (OUTA)
unnamed: R20.2, U3.3 (-IN)
unnamed: R24.2, U4.4 (INA)
unnamed: R25.2, U4.10 (INB)
unnamed: R26.2, U4.7 (PWM)
PWM: R23.2, R26.1; also elsewhere on the board
V_MAIN: R20.1, R21.1, U3.5 (V+); also elsewhere on the board
nMOTOR-FAULT-A: U4.5 (EN/DIAA); also elsewhere on the board
nMOTOR-FAULT-B: U4.9 (EN/DIAB); also elsewhere on the board

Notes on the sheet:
Maximum standby current with all faults cleared is 15uA.
MOTOR CURRENT MEASUREMENT: Motor current is proportional to the voltage developed across R22. This is VOUT. VOUT = voltage across R21 * (R22/R20). Adjust the voltage span (and therefore the current measurement range) by fine tuning R22. Note that the value for R21 will allow accurate current measur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

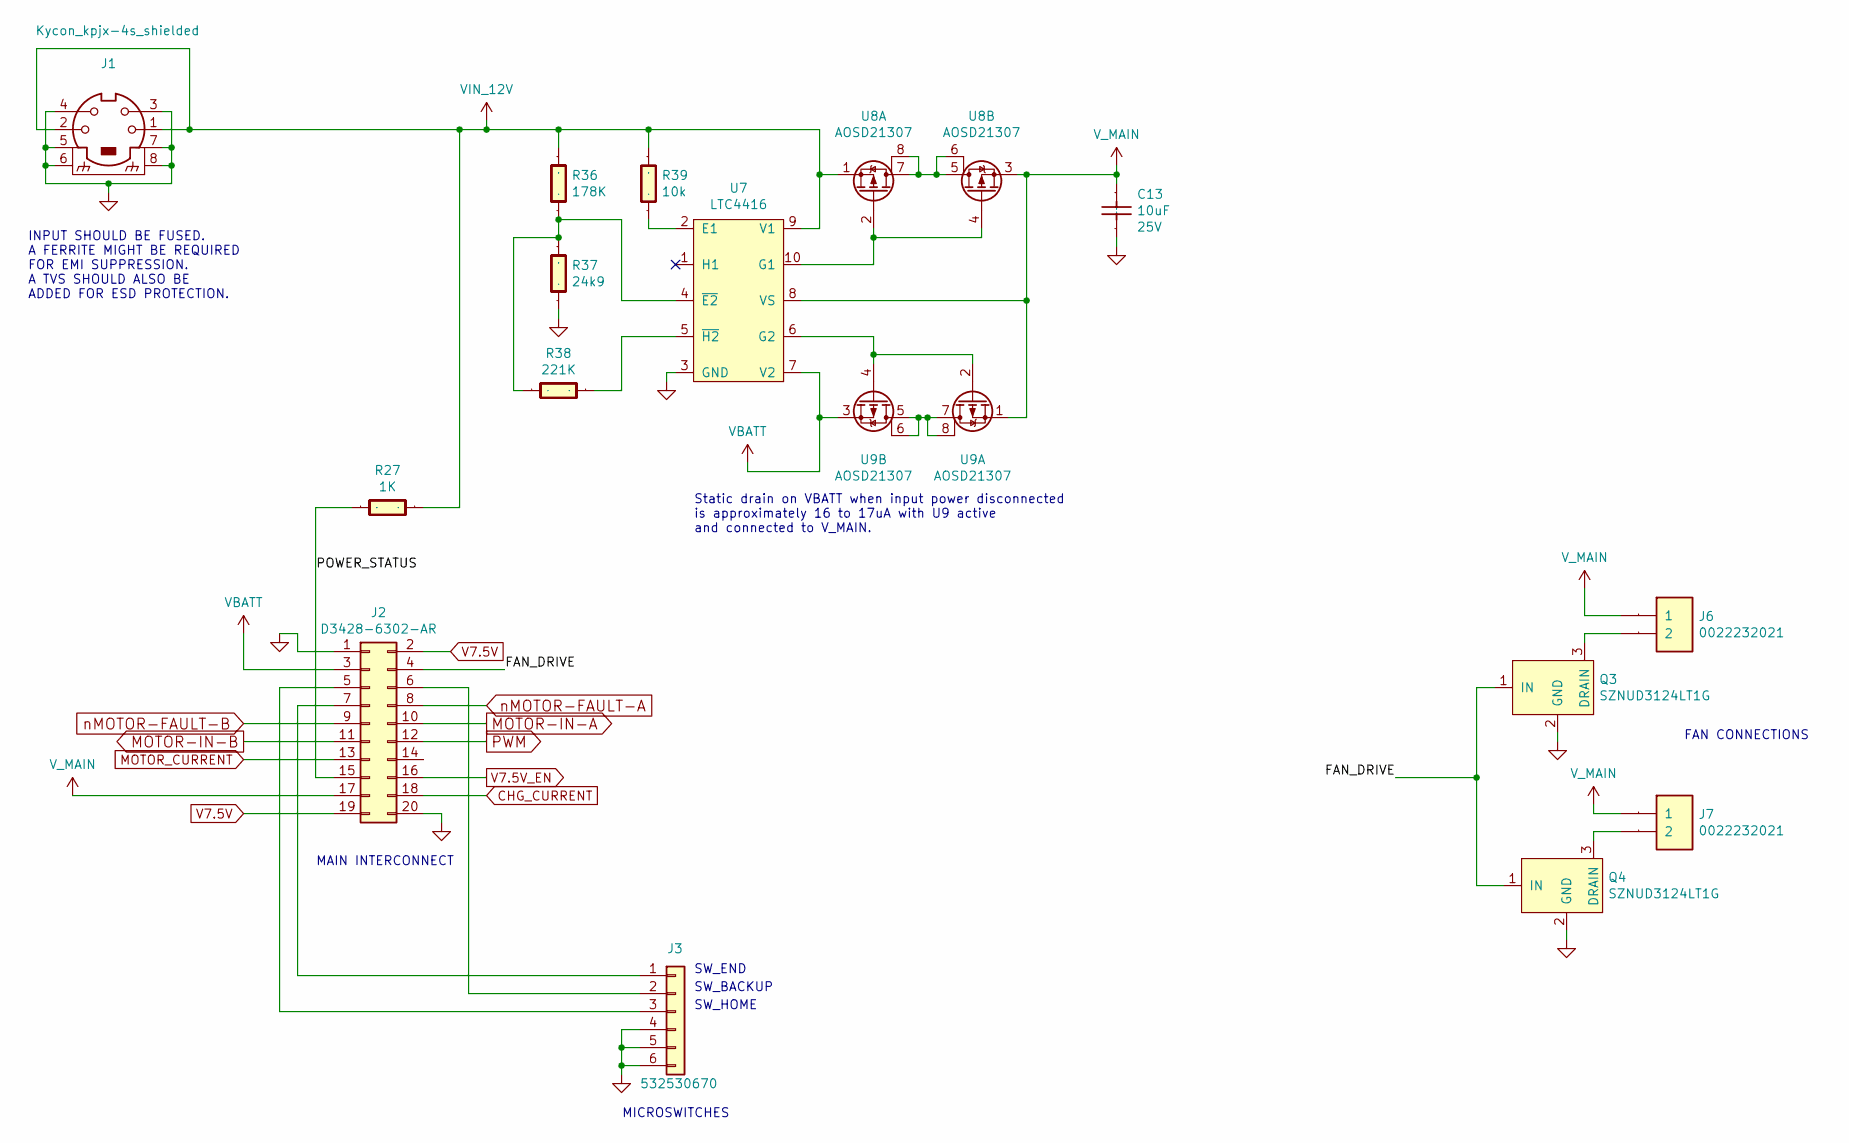
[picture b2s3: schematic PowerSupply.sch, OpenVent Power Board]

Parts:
C13: C_1210_10uF_25V_10%_X7R; C_1210_3225Metric; Voltage 25V; Tolerance 10%; Mfr_PN CL32A106KAULNNE
J1: Kycon_kpjx-4s_shielded; Kycon_KPJX-4S_SHIELD; Mfr_PN KPJX-4S-S
J2: Conn_HDR_2x10_latching; 3M_D3428-6302-AR; Mfr_PN D3428-6302-AR
J3: 532530670; Molex_Micro-Latch_53253-0670_1x06_P2.00mm_Vertical; Mfr_PN 0532530670
J6, J7: CONN_HEADER_2.54X2_MOLEX_KK_Series; Molex_KK-254_AE-6410-02A_1x02_P2.54mm_Vertical; Mfr_PN 0022232021
Q3, Q4: SZNUD3124LT1G; SOT-23; Voltage 12V; Mfr_PN SZNUD3124LT1G
R27: 1K_0603_Chip_Resistor,_1%,_0.1W; R_0603_1608Metric; Tolerance 1%
R36: R_0603_178K_0.1W_1%; R_0603_1608Metric; Tolerance 1%
R37: R_0603_24k9_0.1W_1%; R_0603_1608Metric; Tolerance 1%
R38: R_0603_221K_0.1W_1%; R_0603_1608Metric; Tolerance 1%
R39: 10k_0603_Chip_Resistor,_1%,_0.1W; R_0603_1608Metric; Tolerance 1%
U7: LTC4416; MSOP-10_3x3mm_P0.5mm; Mfr_PN LTC4416IMS#TRPBF
U8, U9: AOSD21307; SOIC-8_3.9x4.9mm_P1.27mm; Mfr_PN AOSD21307

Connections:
/Power Supply/FAN_DRIVE: J2.4, Q3.1 (IN), Q4.1 (IN)
/Power Supply/POWER_STATUS: J2.15, R27.1
CHG_CURRENT: J2.18; also elsewhere on the board
GND: C13.2, J1.3, J1.4, J1.5, J1.6, J1.7, J1.8, J2.1, J2.20, J3.4, J3.5, J3.6, Q3.2 (GND), Q4.2 (GND), R37.2, U7.3 (GND); also elsewhere on the board
MOTOR-IN-A: J2.10; also elsewhere on the board
MOTOR-IN-B: J2.11; also elsewhere on the board
MOTOR_CURRENT: J2.13; also elsewhere on the board
unnamed: J2.5, J3.3
unnamed: J2.6, J3.2
unnamed: J2.7, J3.1
unnamed: J6.2, Q3.3 (DRAIN)
unnamed: J7.2, Q4.3 (DRAIN)
unnamed: R36.2, R37.1, R38.2, U7.4 (~E2~)
unnamed: R38.1, U7.5 (~H2~)
unnamed: R39.2, U7.2 (E1)
unnamed: U7.6 (G2), U9.2 (G), U9.4 (G)
unnamed: U7.10 (G1), U8.2 (G), U8.4 (G)
unnamed: U8.5 (D), U8.6 (D), U8.7 (D), U8.8 (D)
unnamed: U9.5 (D), U9.6 (D), U9.7 (D), U9.8 (D)
PWM: J2.12; also elsewhere on the board
V7.5V: J2.2, J2.19; also elsewhere on the board
V7.5V_EN: J2.16; also elsewhere on the board
VBATT: J2.3, U7.7 (V2), U9.3 (S); also elsewhere on the board
VIN_12V: J1.1, J1.2, R27.2, R36.1, R39.1, U7.9 (V1), U8.1 (S); also elsewhere on the board
V_MAIN: C13.1, J2.17, J6.1, J7.1, U7.8 (VS), U8.3 (S), U9.1 (S); also elsewhere on the board
nMOTOR-FAULT-A: J2.8; also elsewhere on the board
nMOTOR-FAULT-B: J2.9; also elsewhere on the board

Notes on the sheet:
INPUT SHOULD BE FUSED. A FERRITE MIGHT BE REQUIRED FOR EMI SUPPRESSION. A TVS SHOULD ALSO BE ADDED FOR ESD PROTECTION.
MAIN INTERCONNECT
MICROSWITCHES
Static drain on VBATT when input power disconnected is approximately 16 to 17uA with U9 active and connected to V_MAIN.
FAN CONNECTIONS
SW_END
SW_BACKUP
SW_HOME

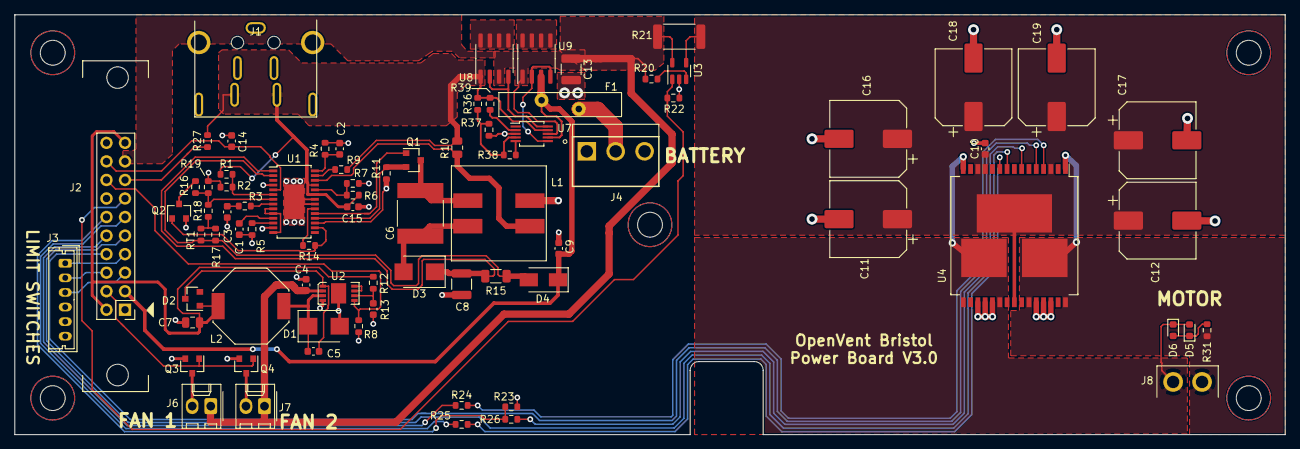
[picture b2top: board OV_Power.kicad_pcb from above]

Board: 2 copper layers, 174.0 x 57.5 mm, 79 parts (0 on the bottom side), 61 nets.
